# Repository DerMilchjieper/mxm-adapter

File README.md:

# mxm-adapter

Research and staged hardware concept for reusing the HP ZBook 17 G5 MXM dGPU connector as an external PCIe/OCuLink host link.

## Current design decision

**RevA targets MXM -> OCuLink x4, not MXM -> external PCIe x16.**

Reasoning:

- x4 keeps the first prototype small enough to route and debug.
- OCuLink provides a mechanically realistic cable exit from a laptop chassis.
- Existing OCuLink eGPU docks can supply the PCIe x16 slot and GPU power externally.
- A passive MXM -> external x16 riser has significantly higher signal-integrity and mechanical risk.
- Dual external GPUs are out of scope for RevA and require either host bifurcation that HP has not documented or an active PCIe switch.

## Safety boundary

Do **not** power a desktop PCIe slot or desktop GPU from the notebook MXM rails. The external GPU dock/backplane must have its own ATX/SFX/server PSU. The notebook-side board should only carry PCIe, clock, reset, presence/sideband signals, and protected low-power logic where required.

## Repository layout

```text
.
├── docs/
│   ├── architecture.md
│   ├── assumptions.md
│   ├── dual-gpu-feasibility.md
│   ├── risk-register.md
│   └── validation-plan.md
├── hardware/
│   └── revA-mxm-to-oculink-x4/
│       ├── block-diagram.md
│       ├── netmap.csv
│       ├── schematic-concept.md
│       ├── stackup-and-layout-rules.md
│       └── bom-categories.md
└── README.md
```

## RevA milestone goals

1. Build a passive/mostly-passive MXM Type-B host-side interposer concept.
2. Route PCIe lanes 0-3, REFCLK, PERST#, CLKREQ#, WAKE#, SMBus, PRSNT and selected power-state signals to an OCuLink 4i connector.
3. Keep GPU slot power fully outside the laptop.
4. Validate boot behavior, PCIe enumeration, link width and link speed before attempting x8/x16.

## Non-goals for RevA

- No hotplug support.
- No desktop PCIe slot inside the notebook.
- No x8/x16 cable riser.
- No dual-GPU switch board.
- No attempt to spoof a full HP MXM GPU module unless measurements prove HP EC/BIOS requires it.

## Status

Concept-only. Not fabrication-ready. HP-specific MXM socket behavior must be measured on the actual ZBook 17 G5 before PCB release.

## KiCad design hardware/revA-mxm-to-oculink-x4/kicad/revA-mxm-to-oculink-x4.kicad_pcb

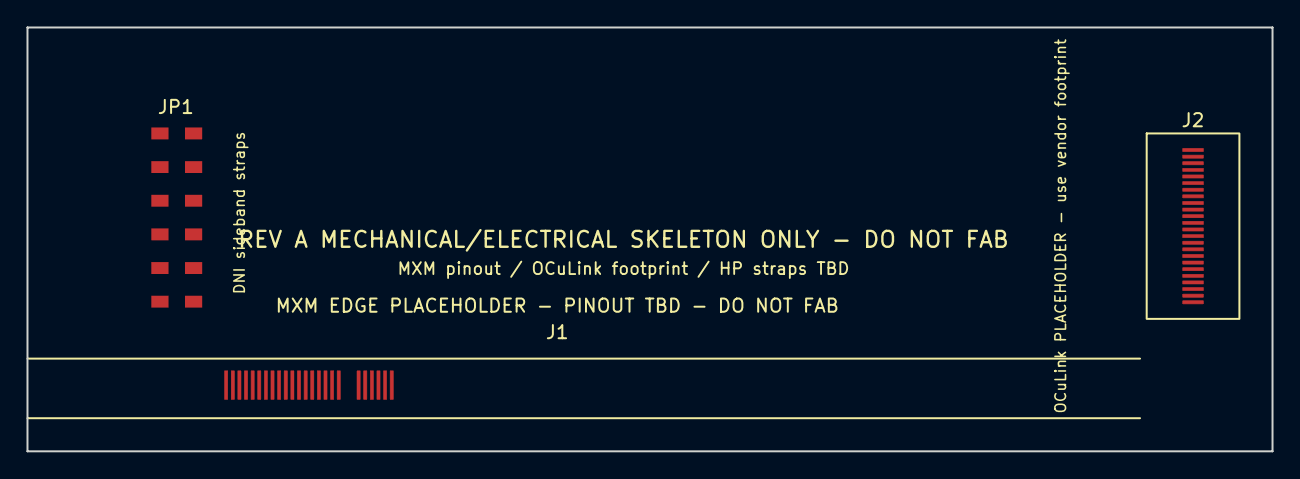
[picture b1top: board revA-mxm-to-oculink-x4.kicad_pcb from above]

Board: 6 copper layers, 94.0 x 32.0 mm, 3 parts (0 on the bottom side), 24 nets, no tracks yet.

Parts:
J1: MXM3_TYPE_B_EDGE_PLACEHOLDER; MXM3_TYPE_B_EDGE_PLACEHOLDER_DO_NOT_FAB
J2: OCuLink_4i_PLACEHOLDER; OCULINK_4I_PLACEHOLDER_DO_NOT_FAB
JP1: DNI_STRAPS; SIDEBAND_STRAP_MATRIX_0603_PLACEHOLDER

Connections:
CLKREQ_N_TBD: J1.A41, J2.CLKREQ, JP1.CLKREQ_N_TBD_A
PCIE_RX0_N_TBD: J1.A23, J2.RX0N
PCIE_RX0_P_TBD: J1.A22, J2.RX0P
PCIE_RX1_N_TBD: J1.A27, J2.RX1N
PCIE_RX1_P_TBD: J1.A26, J2.RX1P
PCIE_RX2_N_TBD: J1.A31, J2.RX2N
PCIE_RX2_P_TBD: J1.A30, J2.RX2P
PCIE_RX3_N_TBD: J1.A35, J2.RX3N
PCIE_RX3_P_TBD: J1.A34, J2.RX3P
PCIE_TX0_N_TBD: J1.A21, J2.TX0N
PCIE_TX0_P_TBD: J1.A20, J2.TX0P
PCIE_TX1_N_TBD: J1.A25, J2.TX1N
PCIE_TX1_P_TBD: J1.A24, J2.TX1P
PCIE_TX2_N_TBD: J1.A29, J2.TX2N
PCIE_TX2_P_TBD: J1.A28, J2.TX2P
PCIE_TX3_N_TBD: J1.A33, J2.TX3N
PCIE_TX3_P_TBD: J1.A32, J2.TX3P
PERST_N_TBD: J1.A40, J2.PERST, JP1.PERST_N_TBD_A
PRSNT_DETECT_TBD: J1.A45, J2.PRSNT, JP1.PRSNT_DETECT_TBD_A
REFCLK_N_TBD: J1.A37, J2.REFN
REFCLK_P_TBD: J1.A36, J2.REFP
SMB_CLK_TBD: J1.A43, J2.SCL, JP1.SMB_CLK_TBD_A
SMB_DATA_TBD: J1.A44, J2.SDA, JP1.SMB_DATA_TBD_A
WAKE_N_TBD: J1.A42, J2.WAKE, JP1.WAKE_N_TBD_A

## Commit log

2026-05-12 Document RevA MXM to OCuLink adapter concept
2026-05-12 Add design assumptions
2026-05-12 Add adapter architecture overview
2026-05-12 Add RevA block diagram
2026-05-12 Add preliminary RevA netmap
2026-05-12 Add RevA schematic concept
2026-05-12 Add stackup and layout rules
2026-05-12 Add BOM categories
2026-05-12 Add validation plan
2026-05-12 Add dual GPU feasibility analysis
2026-05-12 Add risk register
2026-05-12 Add staged roadmap
2026-05-12 Add KiCad layout notes
2026-05-12 Add KiCad project skeleton
2026-05-12 Add KiCad schematic stub
2026-05-12 Add KiCad PCB layout skeleton
2026-05-12 Add KiCad symbol library for RevA
2026-05-12 Add HP MXM pin verification matrix
2026-05-12 Add full RevA layout plan
2026-05-12 Expand KiCad schematic documentation stub
